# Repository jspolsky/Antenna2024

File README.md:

Future Turtles 2024 Public LED Display
====

For the Future Turtles 44' LED mast this year, I'm hoping to improve the array of short, 6' tall "whips" that accompany it.

* I want to have 24 whips instead of 12 whips
* They will be about 3' apart instead of 6', so the patterns will be more interesting
* I plan to improve the cabling substantially, allowing the whips to be daisy-chained instead of each having a cable connecting it all the way back to the controller.

To make the daisy chaining work, each whip will have it's own mini control box sitting at its feet.

* The mini control box will have a Teensy 4.0 to receive commands from the main controller and display things on the LEDs.
* Power will be daisy-chained too. To minimize voltage drop, the power will be transmitted at 24 volts. Each control box will have a tiny 24 volt -> 12 volt DC transformer to power the LEDs and an even smaller 12 volt -> 5 volt buck converter to power its Teensy.
* The data will be sent from the controller over a single RS-485 bus which can be daisy-chained from one mini control box to the next.

Right now I am working on the code in **Whips** which runs on a Teensy 4.1 in the main control box, and on all the Teensy 4.0s in the mini control boxes.

In the main control box it runs in "DOM" mode (#define DOM) and sends commands to the mini control boxes. The mini control boxes run in "SUB" mode (#define SUB) where they receive these commands and are responsible for the LED display of a single whip.

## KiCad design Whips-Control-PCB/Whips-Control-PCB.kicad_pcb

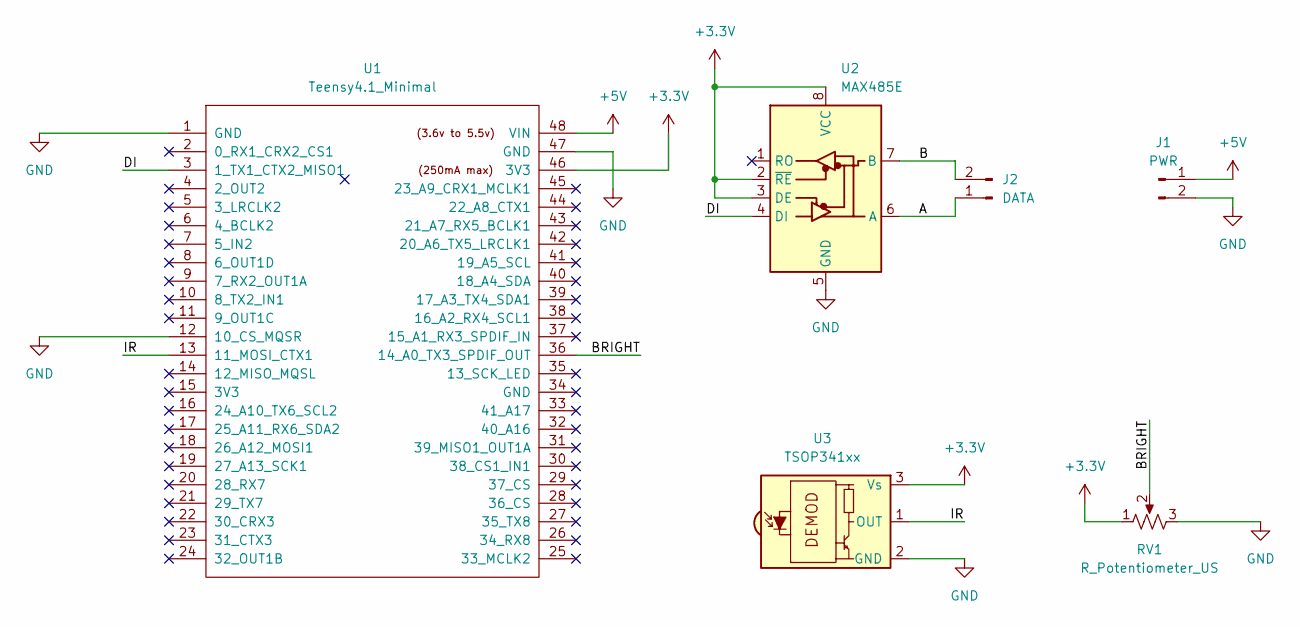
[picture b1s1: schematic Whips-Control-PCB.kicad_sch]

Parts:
J1: PWR; PhoenixContact_MSTBA_2,5_2-G-5,08_1x02_P5.08mm_Horizontal
J2: DATA; PhoenixContact_MSTBA_2,5_2-G-5,08_1x02_P5.08mm_Horizontal
RV1: R_Potentiometer_US; Potentiometer_Alpha_RD901F-40-00D_Single_Vertical
U1: Teensy4.1_Minimal; Teensy41_Minimal
U2: MAX485E; Max485-Module
U3: TSOP341xx; Vishay_MOLD-3Pin

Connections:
+3.3V: RV1.1, U1.46 (3V3), U2.2 (~RE), U2.3 (DE), U2.8 (VCC), U3.3 (Vs)
+5V: J1.1, U1.48 (VIN)
/A: J2.1, U2.6 (A)
/B: J2.2, U2.7 (B)
/BRIGHT: RV1.2, U1.36 (14_A0_TX3_SPDIF_OUT)
/DI: U1.3 (1_TX1_CTX2_MISO1), U2.4 (DI)
/IR: U1.13 (11_MOSI_CTX1), U3.1 (OUT)
GND: J1.2, RV1.3, U1.1 (GND), U1.12 (10_CS_MQSR), U1.47 (GND), U2.5 (GND), U3.2 (GND)

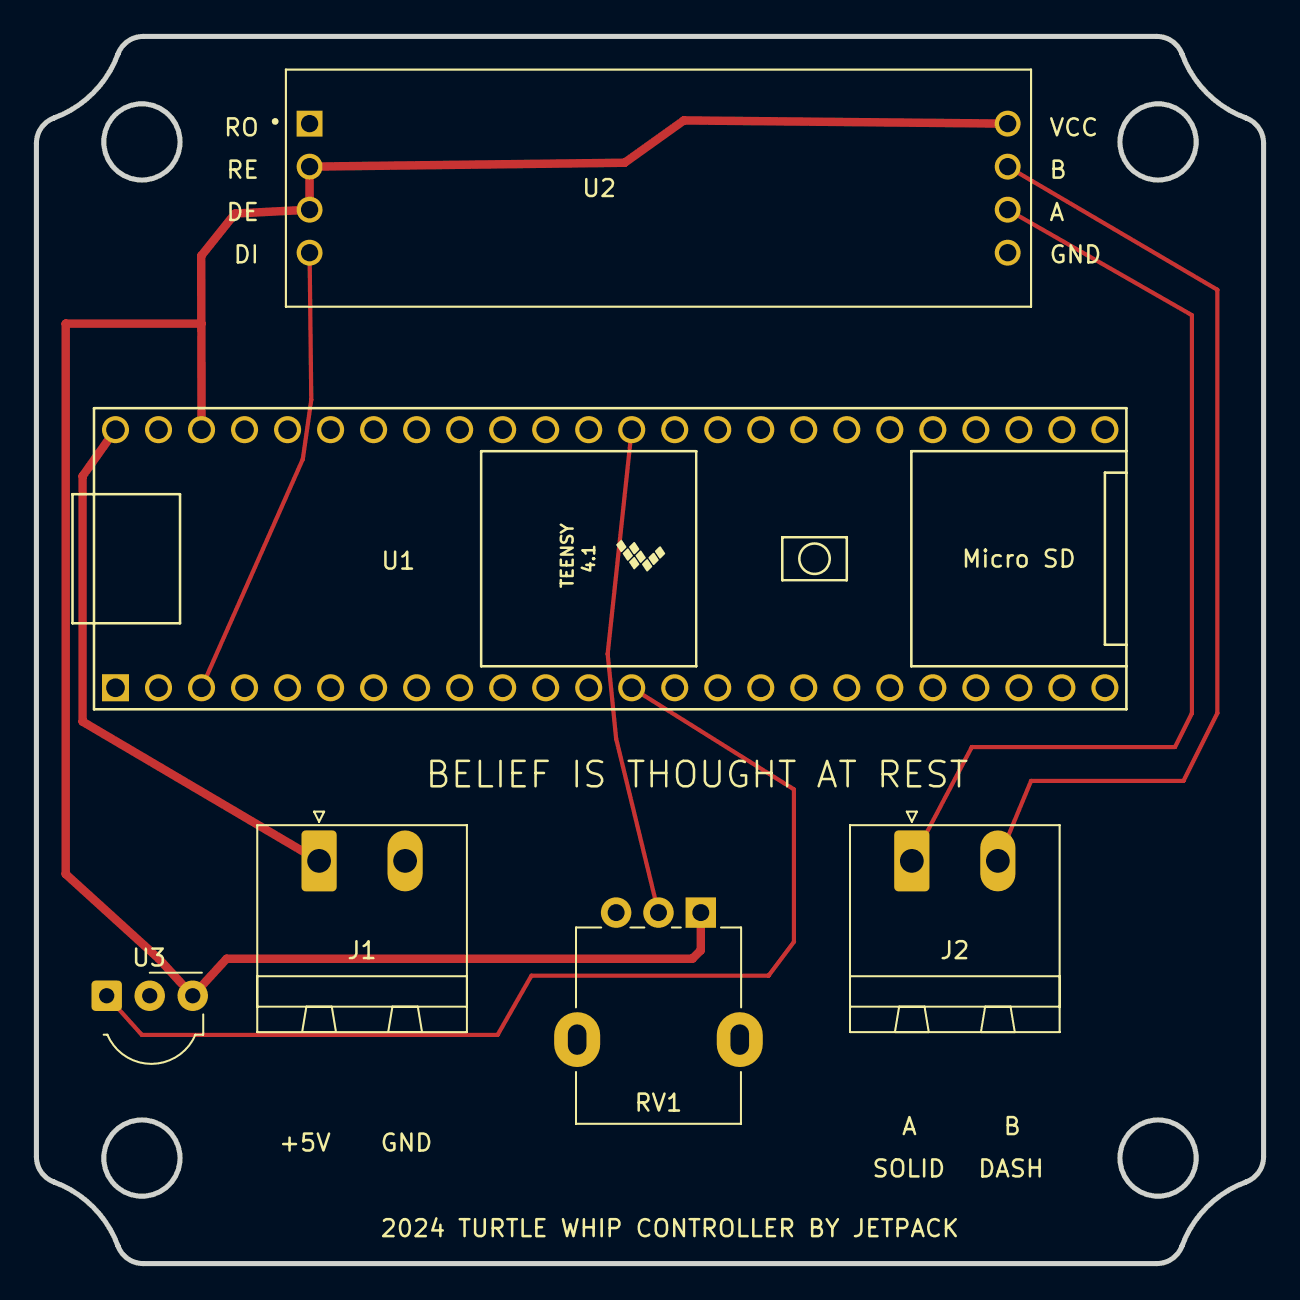
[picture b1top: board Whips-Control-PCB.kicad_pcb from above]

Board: 2 copper layers, 72.5 x 72.5 mm, 6 parts (0 on the bottom side), 8 nets.

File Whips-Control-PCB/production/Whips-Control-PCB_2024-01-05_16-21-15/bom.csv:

Designator,Footprint,Quantity,Value,LCSC Part #
J1,"PhoenixContact_MSTBA_2,5_2-G-5,08_1x02_P5.08mm_Horizontal",1,PWR,
J2,"PhoenixContact_MSTBA_2,5_2-G-5,08_1x02_P5.08mm_Horizontal",1,DATA,
RV1,Potentiometer_Alpha_RD901F-40-00D_Single_Vertical,1,R_Potentiometer_US,
U1,Teensy41_Minimal,1,Teensy4.1_Minimal,
U2,Max485-Module,1,MAX485E,
U3,Vishay_MOLD-3Pin,1,TSOP341xx,

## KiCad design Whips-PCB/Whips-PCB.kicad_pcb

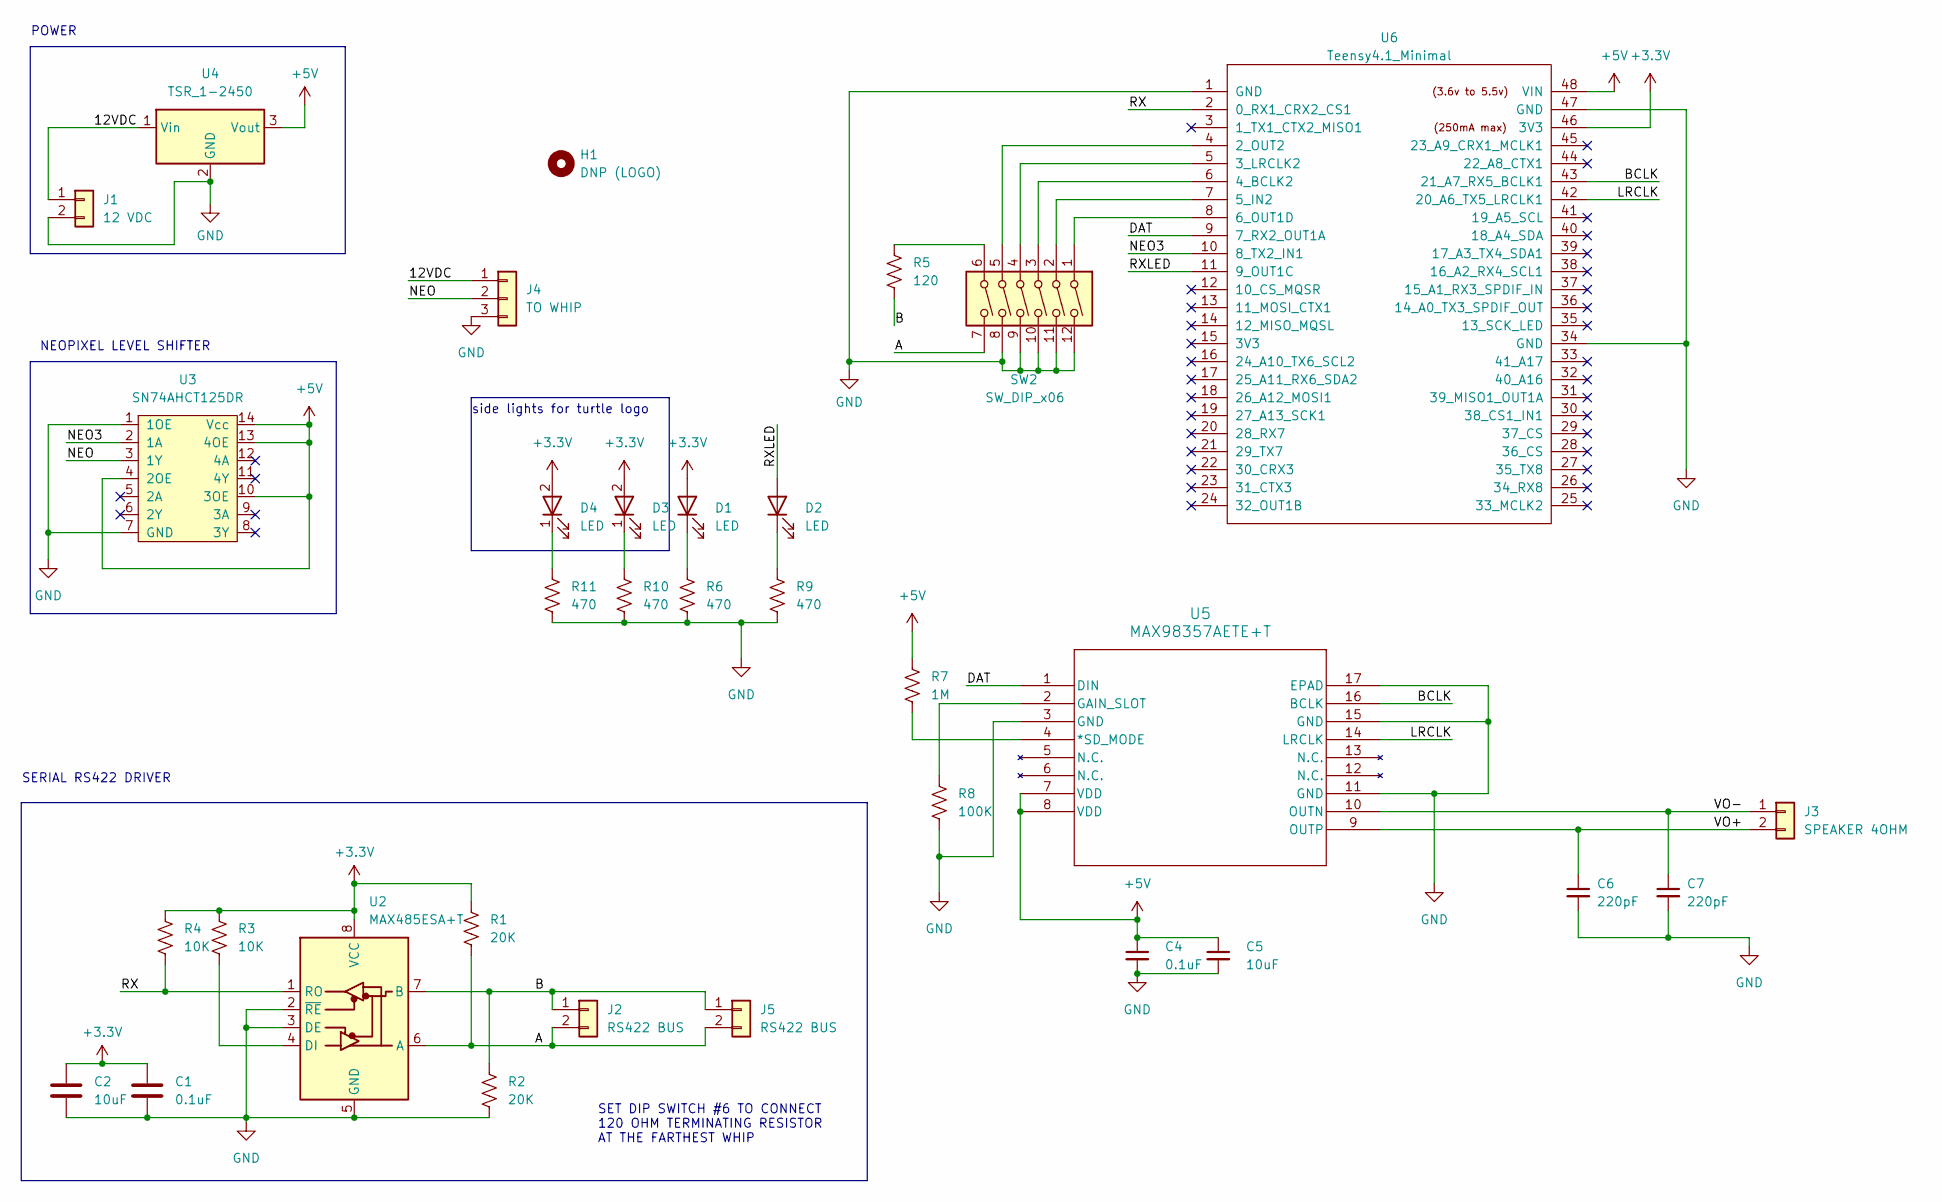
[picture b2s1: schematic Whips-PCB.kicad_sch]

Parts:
C1, C4: 0.1uF; C_0402_1005Metric; LCSC C1525
C2, C5: 10uF; C_0402_1005Metric; LCSC C15525
C6, C7: 220pF; C_0402_1005Metric; LCSC C1530
D1: LED; LED_0603_1608Metric; LCSC C2286
D2: LED; LED_0603_1608Metric; LCSC C2290
D3, D4: LED; Everlight 99-218GLM2C-L7277SGU-TR8-T0-ES side view LED; LCSC C605463
H1: DNP (LOGO); Turtle-Art-2024
J1: 12 VDC; TerminalBlock_Phoenix_MKDS-1,5-2_1x02_P5.00mm_Horizontal; LCSC C8404
J2, J5: RS422 BUS; TerminalBlock_Phoenix_MKDS-1,5-2_1x02_P5.00mm_Horizontal; LCSC C8404
J3: SPEAKER 4OHM; TerminalBlock_Phoenix_MKDS-1,5-2_1x02_P5.00mm_Horizontal; LCSC C8404
J4: TO WHIP; TerminalBlock_Phoenix_MKDS-1,5-3_1x03_P5.00mm_Horizontal; LCSC C8401
R1, R2: 20K; R_0603_1608Metric; LCSC C4184
R3, R4: 10K; R_0603_1608Metric; LCSC C25804
R5: 120; R_0402_1005Metric; LCSC C25079
R6, R9, R10, R11: 470; R_0402_1005Metric; LCSC C25117
R7: 1M; R_0402_1005Metric; LCSC C26083
R8: 100K; R_0402_1005Metric; LCSC C25741
SW2: SW_DIP_x06; SW_DIP_SPSTx06_Slide_6.7x16.8mm_W7.62mm_P2.54mm_LowProfile; LCSC C2859410
U2: MAX485ESA+T; SOIC-8_3.9x4.9mm_P1.27mm; LCSC C19738
U3: SN74AHCT125DR; SOIC-14_3.9x8.7mm_P1.27mm; LCSC C155176
U4: TSR_1-2450; Converter_DCDC_TRACO_TSR-1_THT; LCSC DNP
U5: MAX98357AETE+T; LCSC C910544
U6: Teensy4.1_Minimal; Teensy41_Minimal; LCSC DNP

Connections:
+3.3V: C1.1, C2.1, D1.2 (A), D3.2 (A), D4.2 (A), R1.1, R3.1, R4.1, U2.8 (VCC), U6.46 (3V3)
+5V: C4.1, C5.1, R7.1, U3.4 (2OE), U3.10 (3OE), U3.13 (4OE), U3.14 (Vcc), U4.3 (Vout), U5.7 (VDD), U5.8 (VDD), U6.48 (VIN)
/12VDC: J1.1, J4.1, U4.1 (Vin)
/A: J2.2, J5.2, R1.2, SW2.7, U2.6 (A)
/B: J2.1, J5.1, R2.2, R5.2, U2.7 (B)
/BCLK: U5.16 (BCLK), U6.43 (21_A7_RX5_BCLK1)
/DAT: U5.1 (DIN), U6.9 (7_RX2_OUT1A)
/LRCLK: U5.14 (LRCLK), U6.42 (20_A6_TX5_LRCLK1)
/NEO: J4.2, U3.3 (1Y)
/NEO3: U3.2 (1A), U6.10 (8_TX2_IN1)
/RX: R4.2, U2.1 (RO), U6.2 (0_RX1_CRX2_CS1)
/RXLED: D2.2 (A), U6.11 (9_OUT1C)
/VO+: C6.1, J3.2, U5.9 (OUTP)
/VO-: C7.1, J3.1, U5.10 (OUTN)
GND: C1.2, C2.2, C4.2, C5.2, C6.2, C7.2, J1.2, J4.3, R2.1, R6.2, R8.2, R9.2, R10.2, R11.2, SW2.8, SW2.9, SW2.10, SW2.11, SW2.12, U2.2 (~RE), U2.3 (DE), U2.5 (GND), U3.1 (1OE), U3.7 (GND), U4.2 (GND), U5.3 (GND), U5.11 (GND), U5.15 (GND), U5.17 (EPAD), U6.1 (GND), U6.34 (GND), U6.47 (GND)
unnamed: D1.1 (K), R6.1
unnamed: D2.1 (K), R9.1
unnamed: D3.1 (K), R10.1
unnamed: D4.1 (K), R11.1
unnamed: R5.1, SW2.6
unnamed: R3.2, U2.4 (DI)
unnamed: R7.2, U5.4 (*SD_MODE)
unnamed: R8.1, U5.2 (GAIN_SLOT)
unnamed: SW2.5, U6.4 (2_OUT2)
unnamed: SW2.4, U6.5 (3_LRCLK2)
unnamed: SW2.3, U6.6 (4_BCLK2)
unnamed: SW2.2, U6.7 (5_IN2)
unnamed: SW2.1, U6.8 (6_OUT1D)

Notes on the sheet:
POWER
SERIAL RS422 DRIVER
side lights for turtle logo
NEOPIXEL LEVEL SHIFTER
SET DIP SWITCH #6 TO CONNECT 120 OHM TERMINATING RESISTOR AT THE FARTHEST WHIP

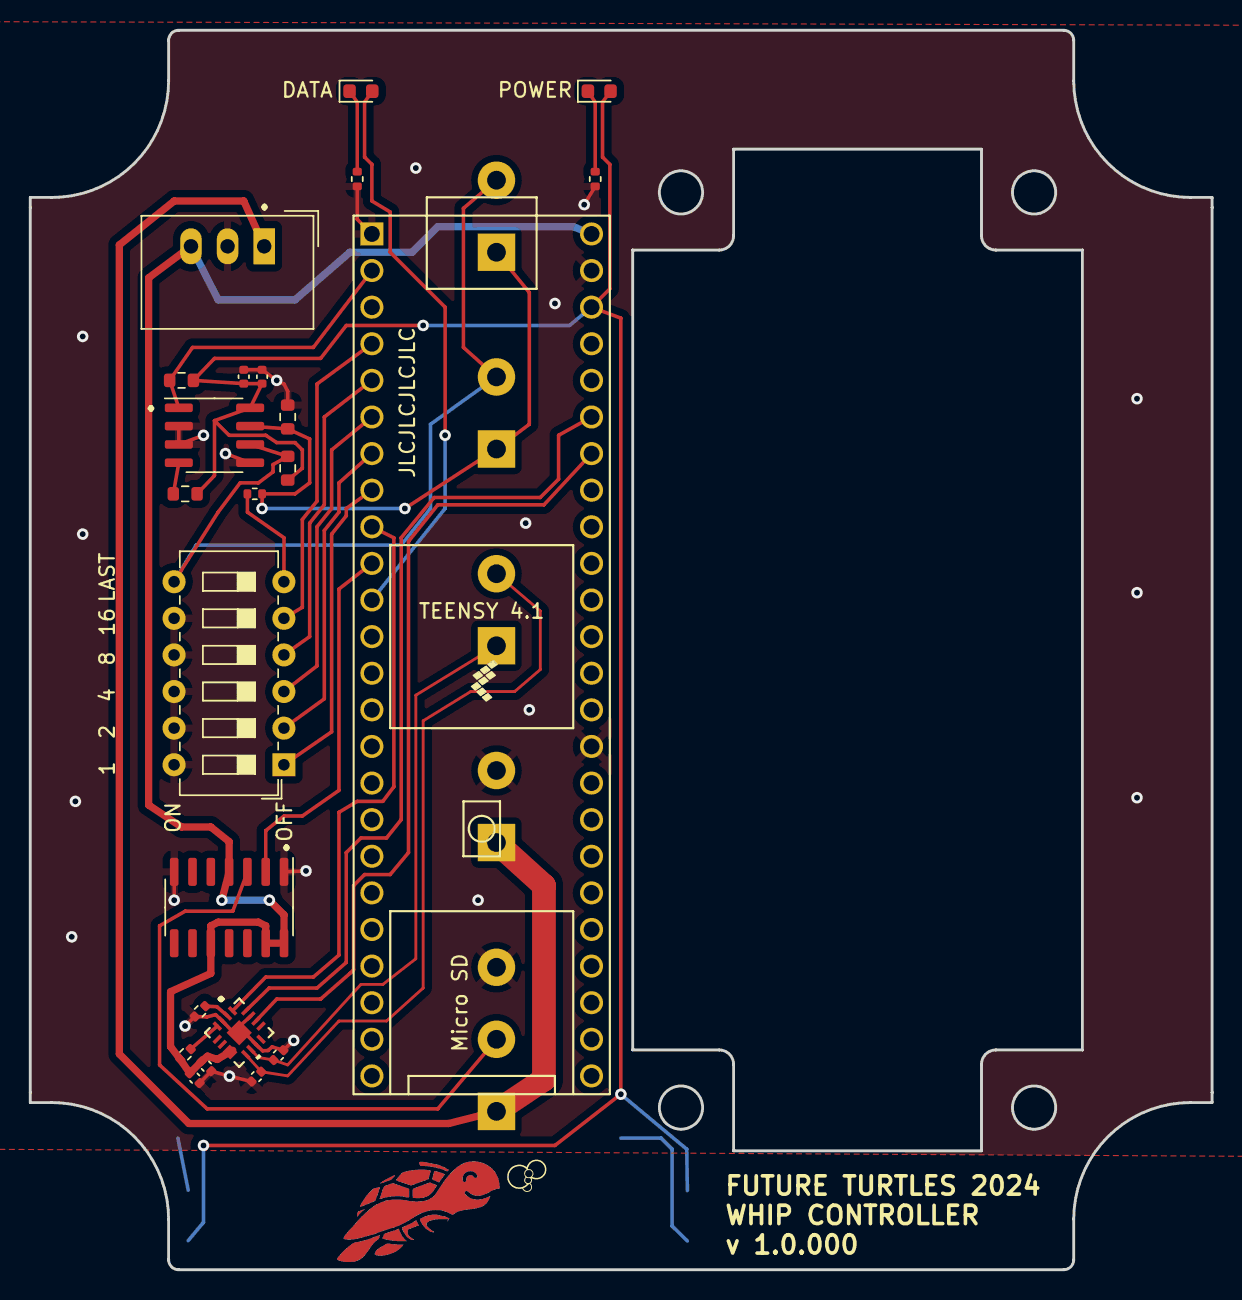
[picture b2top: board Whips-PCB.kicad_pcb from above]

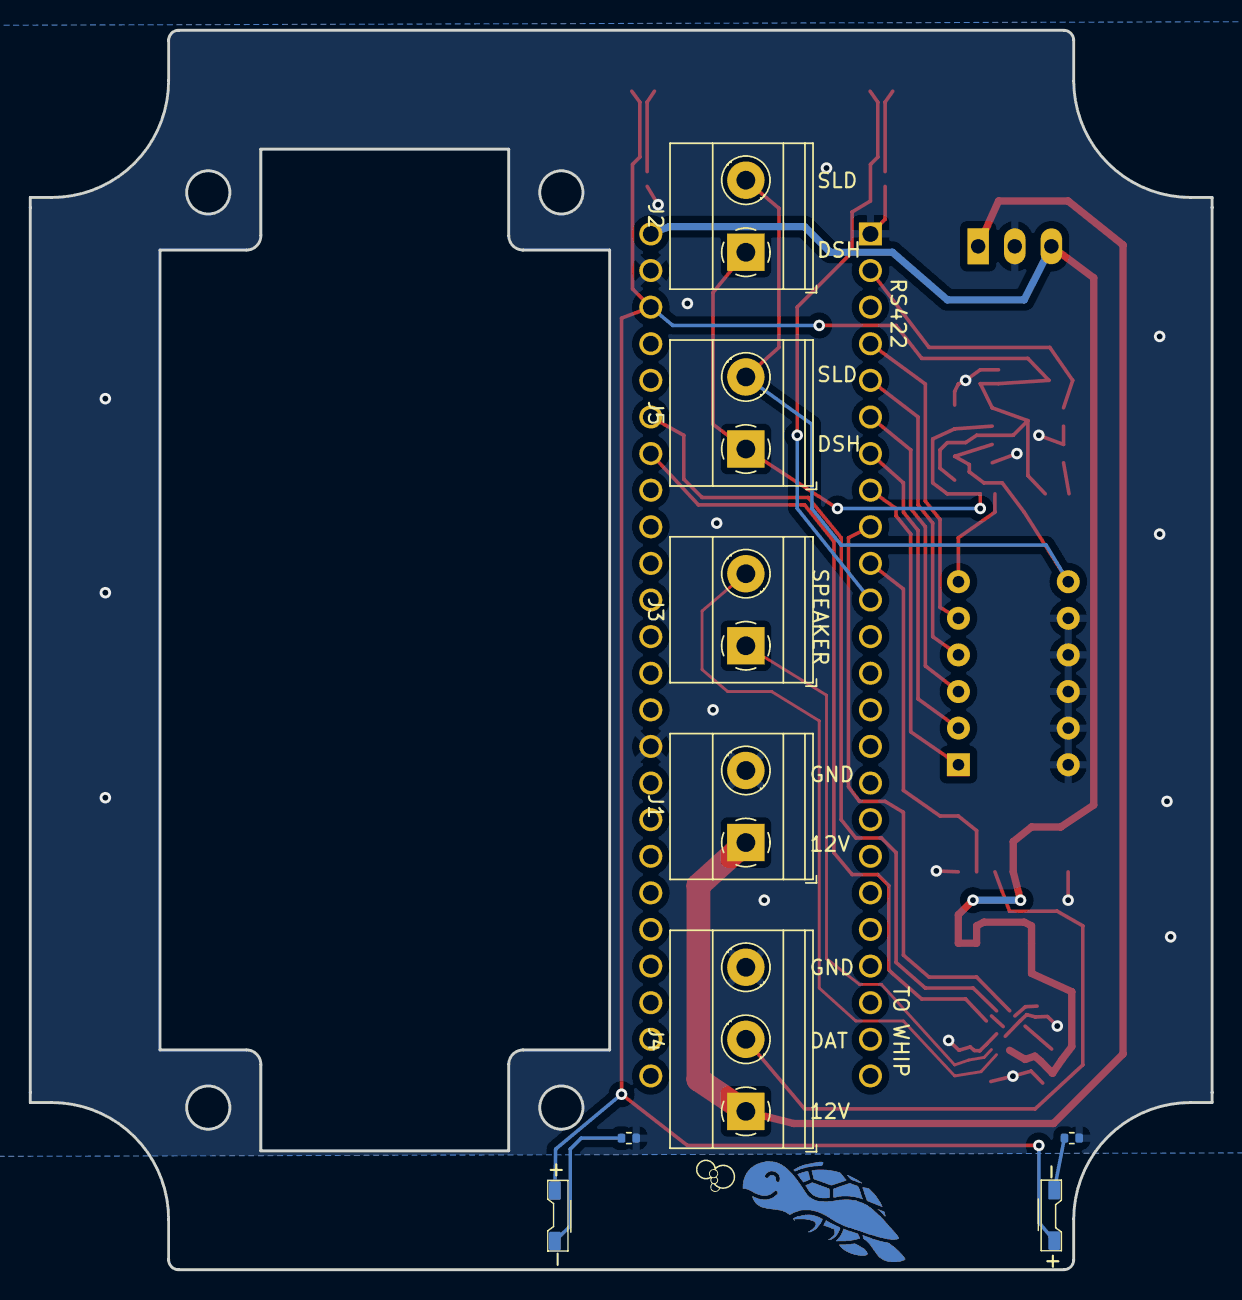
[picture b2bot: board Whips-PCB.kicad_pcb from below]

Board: 2 copper layers, 82.0 x 86.0 mm, 33 parts (9 on the bottom side), 28 nets.

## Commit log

2023-10-25 readme
2023-10-25 typo
2023-10-26 Incorporate FastLED
2023-10-26 lovely hack needed to use Serial coms and WS2812 at the same time
2023-10-27 a little basic refactoring
2023-10-27 little bit of refactoring
2023-10-27 further refactoring
2023-10-27 more modern preprocessor directives
2023-10-27 added PacketSerial code. Having trouble with colors other than primary
2023-10-27 ok got it working - problem was level shifter in hardware
2023-10-27 even smöler paqette
2023-10-27 Packets, Checksums, and a nice architecture for serial communications
2023-11-02 Dip Switches to determine whip address
2023-11-03 Schematics for whips controller - everything but audio
2023-11-03 improved rs422
2023-11-06 refactoring and test SD card code
2023-11-06 StatusLed conflicts with SPI
2023-11-06 Got some basic sound playing working!
2023-11-06 updated schematic to reflect audio and sd card
2023-11-07 tweaks
2023-11-07 minor cleanup
2023-11-07 Refactored; now playing sounds from the DOM
2023-11-07 volume adjustment. Use maximum gain in hardware
2023-11-08 save space with CRC16 instead of CRC32
2023-11-08 pack structures on the wire to save bytes!
2023-11-08 objectified who commands work for easier use
2023-11-08 allow commands to change and be resent with new crc
2023-11-08 cleaned up packet sending
2023-11-08 experiment with new boop
2023-11-09 pots for brightness (not implemented), volume
2023-11-09 setBrightness is in the protocol
2023-11-09 teensy 4.0->4.1
2023-11-09 starting to find part numbers and footprints
2023-11-17 support for indicator LEDS
2023-11-17 provided parts and footprints for LEDs
2023-11-19 full PCB - everything except decorations
2023-11-19 cute turtle logo
2023-11-20 Much better turtle logo with backlights
2023-11-22 Latest PCBs and some new gitignore stuff
2023-11-26 Stub GIF reading code is working
2023-11-26 revamped, parallelized etc
2023-11-27 fix bug in preview; rotate final images 90 right
2023-11-27 kinda got gif decoding working
2023-11-27 new commands for Animated GIFs; fixed checksum bug
2023-11-27 framework for animated gif from dom to sub
2023-11-27 Eliminate DOM/SUB compile options. Mode determined at runtime
2023-11-28 figgered out last bug in rendering animated gifs!
2023-11-28 stuff arrived
2023-11-29 Perf
2023-11-29 some sample/test gif animations
2023-11-29 minimum IR for controlling dom
2023-12-19 Speakers didn't work. No sound
2023-12-19 no speakers? no volume
2023-12-19 resume brightness control
2023-12-19 Every gif frame packet includes gif #
2023-12-19 ignored stuff
2023-12-19 ability to toggle to next gif
2023-12-27 debugging commands (rgbw, selfid)
2023-12-27 faster start. SUB without DOM shows orange
2023-12-27 Use ACTUAL gif speed
2023-12-27 whip > 23? no. no such thing
2024-01-23 PCB for controller
2024-01-23 remote instead of pots for brightness
2024-01-23 fewer brightness steps
2024-01-23 use EEPROM to remember brightness
2024-01-23 new animation every 20 seconds
2024-01-24 visual indication of brightness change
